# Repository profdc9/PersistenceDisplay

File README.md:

Persistence Display.  More details to come soon.

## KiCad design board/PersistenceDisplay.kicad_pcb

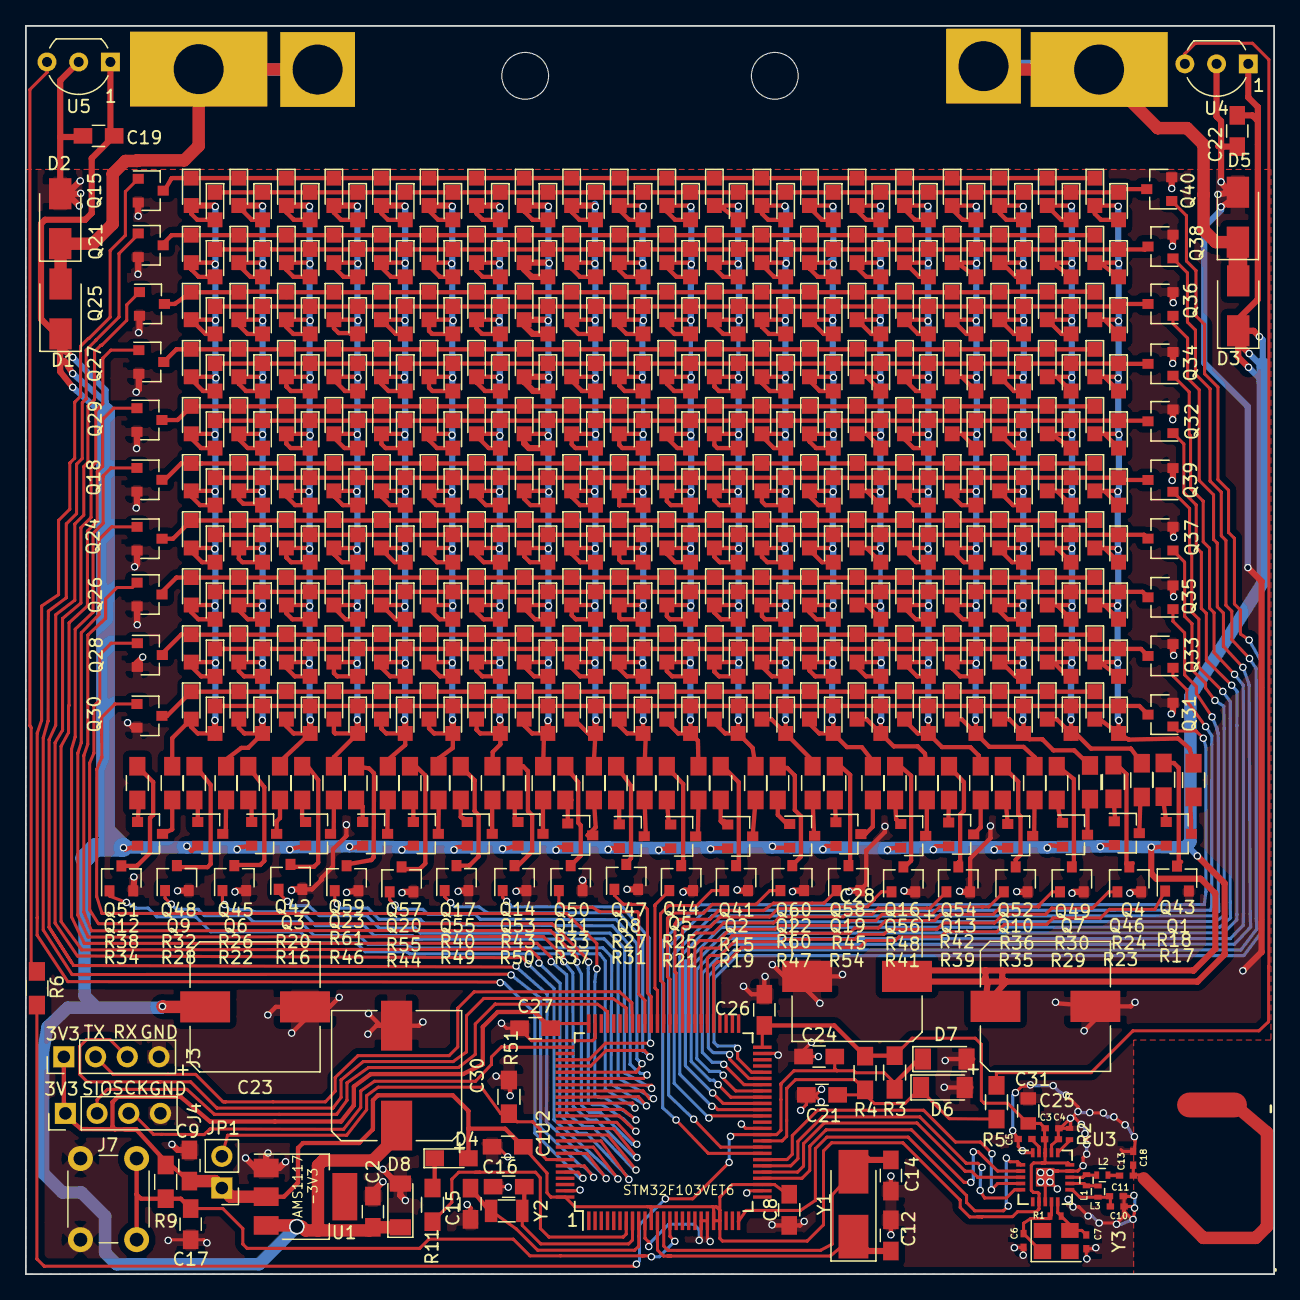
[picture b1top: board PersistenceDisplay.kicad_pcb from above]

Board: 2 copper layers, 100.0 x 100.0 mm, 567 parts (0 on the bottom side), 175 nets.

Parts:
C1, C2: 1 uF; C_0805_HandSoldering
C3: 10 nF; C_0402_NoSilk
C4: 1 nF; C_0402_NoSilk
C5: 33 nF; C_0402_NoSilk
C6, C7: 22 pF; C_0402_NoSilk
C8, C9, C19, C22, C26, C27: 0.1 uF; C_0805_HandSoldering
C10: 2.2 nF; C_0402_NoSilk
C11: 4.7 pF; C_0402_NoSilk
C12, C14, C15, C16: 20 pF; C_0805_HandSoldering
C13: 1.5 pF; C_0402_NoSilk
C17: 10 nF; C_0805_HandSoldering
C18: 1 pF; C_0402_NoSilk
C21, C24: 22 pF; C_0805_HandSoldering
C23, C25, C28, C30: 1000 uF; CP_Elec_10x10.5
C31: 4.7 uF; C_0805
D1, D2, D3, D5: SS34; D_SMA
D4: LED; LED_0805_HandSoldering
D6, D7: 3.3V; D_MiniMELF
D8: 5.6V; D_MiniMELF
D9, D10, D11, D12, D13, D14, D15, D16, D17, D18, D19, D20, D21, D22, D23, D24, D25, D26, D27, D28, D29, D30, D31, D32, D33, D34, D35, D36, D37, D38, D39, D40, D41, D42, D43, D44, D45, D46, D47, D48, D49, D50, D51, D52, D53, D54, D55, D56, D57, D58, D59, D60, D61, D62, D63, D64, D65, D66, D67, D68, D69, D70, D71, D72, D73, D74, D75, D76, D77, D78, D79, D80, D81, D82, D83, D84, D85, D86, D87, D88, D89, D90, D91, D92, D93, D94, D95, D96, D97, D98, D99, D100, D101, D102, D103, D104, D105, D106, D107, D108, D109, D110, D111, D112, D113, D114, D115, D116, D117, D118, D119, D120, D121, D122, D123, D124, D125, D126, D127, D128, D129, D130, D131, D132, D133, D134, D135, D136, D137, D138, D139, D140, D141, D142, D143, D144, D145, D146, D147, D148, D149, D150, D151, D152, D153, D154, D155, D156, D157, D158, D159, D160, D161, D162, D163, D164, D165, D166, D167, D168, D169, D170, D171, D172, D173, D174, D175, D176, D177, D178, D179, D180, D181, D182, D183, D184, D185, D186, D187, D188, D189, D190, D191, D192, D193, D194, D195, D196, D197, D198, D199, D200, D201, D202, D203, D204, D205, D206, D207, D208, D209, D210, D211, D212, D213, D214, D215, D216, D217, D218, D219, D220, D221, D222, D223, D224, D225, D226, D227, D228, D229, D230, D231, D232, D233, D234, D235, D236, D237, D238, D239, D240, D241, D242, D243, D244, D245, D246, D247, D248, D249, D250, D251, D252, D253, D254, D255, D256, D257, D258, D259, D260, D261, D262, D263, D264, D265, D266, D267, D268, D269, D270, D271, D272, D273, D274, D275, D276, D277, D278, D279, D280, D281, D282, D283, D284, D285, D286, D287, D288, D289, D290, D291, D292, D293, D294, D295, D296, D297, D298, D299, D300, D301, D302, D303, D304, D305, D306, D307, D308, D309, D310, D311, D312, D313, D314, D315, D316, D317, D318, D319, D320, D321, D322, D323, D324, D325, D326, D327, D328, D329, D330, D331, D332, D333, D334, D335, D336, D337, D338, D339, D340, D341, D342, D343, D344, D345, D346, D347, D348, D349, D350, D351, D352, D353, D354, D355, D356, D357, D358, D359, D360, D361, D362, D363, D364, D365, D366, D367, D368, D369, D370, D371, D372, D373, D374, D375, D376, D377, D378, D379, D380, D381, D382, D383, D384, D385, D386, D387, D388, D389, D390, D391, D392, D393, D394, D395, D396, D397, D398, D399, D400, D401, D402, D403, D404, D405, D406, D407, D408: LED; LED_0805NoLabel
J3, J4: Conn_01x04; Pin_Header_Straight_1x04_Pitch2.54mm
J5, J6, J11, J12: Conn_01x01; ContactPad
J7: Conn_01x02; SW_PUSH_6mm
J8, J9: Conn_01x01; BigSlot
JP1: Jumper; Pin_Header_Straight_1x02_Pitch2.54mm
L1: 8.2 nH; L_0402
L2: 3.9 nH; L_0402
L3: 2.7 nH; L_0402
Q1, Q2, Q3, Q4, Q5, Q6, Q7, Q8, Q9, Q10, Q11, Q12, Q13, Q14, Q15, Q16, Q17, Q18, Q19, Q20, Q21, Q22, Q23, Q24, Q25, Q26, Q27, Q28, Q29, Q30, Q31, Q32, Q33, Q34, Q35, Q36, Q37, Q38, Q39, Q40: 2N7002; SOT-23
Q41, Q42, Q43, Q44, Q45, Q46, Q47, Q48, Q49, Q50, Q51, Q52, Q53, Q54, Q55, Q56, Q57, Q58, Q59, Q60: SS8550; SOT-23
R1: 1M; R_0402_NoSilk
R2: 22k; R_0402_NoSilk
R3, R4: 1k; R_0805_HandSoldering
R5, R6: 150R; R_0805_HandSoldering
R9: 1.5k; R_0805_HandSoldering
R11: 470R; R_0805_HandSoldering
R15, R16, R17, R21, R22, R23, R27, R28, R29, R33, R34, R35, R39, R40, R41, R44, R45, R46, R47, R50: 220R; R_0805_HandSoldering
R18, R19, R20, R24, R25, R26, R30, R31, R32, R36, R37, R38, R42, R43, R48, R49, R51, R54, R55, R60, R61: 10k; R_0805_HandSoldering
U1: AMS1117-3V3; SOT-223
U2: STM32F103VETx; LQFP-100_14x14mm_Pitch0.5mm
U3: nrf24l01; QFN-20-1EP_4x4mm_Pitch0.5mm_smaller_internal_pad
U4, U5: OH137; TO-92_Inline_Wide
Y1: 8 MHz; Crystal_SMD_5032-2pin_5.0x3.2mm_HandSoldering
Y2: 32.768 kHz; Crystal_SMD_3215-2pin_3.2x1.5mm
Y3: 16 MHz; Crystal_SMD_3225-4pin_3.2x2.5mm

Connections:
+3V3: C1.2, C3.2, C4.2, C8.2, C9.2, C26.2, C27.2, C31.2, D4.2, J3.1, J4.1, JP1.1, R3.2, R4.2, R9.1, U1.2, U2.11, U2.21, U2.22, U2.28, U2.50, U2.75, U2.100, U3.7, U3.15, U3.18
+5V: C2.2, C19.2, C22.2, C23.1, C25.1, C28.1, C30.1, D1.1, D3.1, D8.1, Q41.2, Q42.2, Q43.2, Q44.2, Q45.2, Q46.2, Q47.2, Q48.2, Q49.2, Q50.2, Q51.2, Q52.2, Q53.2, Q54.2, Q55.2, Q56.2, Q57.2, Q58.2, Q59.2, Q60.2, U1.3, U4.1, U5.1
COL1: D9.2, D29.2, D49.2, D69.2, D89.2, D109.2, D129.2, D149.2, D169.2, D189.2, D209.2, D229.2, D249.2, D269.2, D289.2, D309.2, D329.2, D349.2, D369.2, D389.2, R17.2
COL2: D10.2, D30.2, D50.2, D70.2, D90.2, D110.2, D130.2, D150.2, D170.2, D190.2, D210.2, D230.2, D250.2, D270.2, D290.2, D310.2, D330.2, D350.2, D370.2, D390.2, R23.2
COL3: D11.2, D31.2, D51.2, D71.2, D91.2, D111.2, D131.2, D151.2, D171.2, D191.2, D211.2, D231.2, D251.2, D271.2, D291.2, D311.2, D331.2, D351.2, D371.2, D391.2, R29.2
COL4: D12.2, D32.2, D52.2, D72.2, D92.2, D112.2, D132.2, D152.2, D172.2, D192.2, D212.2, D232.2, D252.2, D272.2, D292.2, D312.2, D332.2, D352.2, D372.2, D392.2, R35.2
COL5: D13.2, D33.2, D53.2, D73.2, D93.2, D113.2, D133.2, D153.2, D173.2, D193.2, D213.2, D233.2, D253.2, D273.2, D293.2, D313.2, D333.2, D353.2, D373.2, D393.2, R39.2
COL6: D14.2, D34.2, D54.2, D74.2, D94.2, D114.2, D134.2, D154.2, D174.2, D194.2, D214.2, D234.2, D254.2, D274.2, D294.2, D314.2, D334.2, D354.2, D374.2, D394.2, R41.2
COL7: D15.2, D35.2, D55.2, D75.2, D95.2, D115.2, D135.2, D155.2, D175.2, D195.2, D215.2, D235.2, D255.2, D275.2, D295.2, D315.2, D335.2, D355.2, D375.2, D395.2, R45.2
COL8: D16.2, D36.2, D56.2, D76.2, D96.2, D116.2, D136.2, D156.2, D176.2, D196.2, D216.2, D236.2, D256.2, D276.2, D296.2, D316.2, D336.2, D356.2, D376.2, D396.2, R47.2
COL9: D17.2, D37.2, D57.2, D77.2, D97.2, D117.2, D137.2, D157.2, D177.2, D197.2, D217.2, D237.2, D257.2, D277.2, D297.2, D317.2, D337.2, D357.2, D377.2, D397.2, R15.2
COL10: D18.2, D38.2, D58.2, D78.2, D98.2, D118.2, D138.2, D158.2, D178.2, D198.2, D218.2, D238.2, D258.2, D278.2, D298.2, D318.2, D338.2, D358.2, D378.2, D398.2, R21.2
COL11: D19.2, D39.2, D59.2, D79.2, D99.2, D119.2, D139.2, D159.2, D179.2, D199.2, D219.2, D239.2, D259.2, D279.2, D299.2, D319.2, D339.2, D359.2, D379.2, D399.2, R27.2
COL12: D20.2, D40.2, D60.2, D80.2, D100.2, D120.2, D140.2, D160.2, D180.2, D200.2, D220.2, D240.2, D260.2, D280.2, D300.2, D320.2, D340.2, D360.2, D380.2, D400.2, R33.2
COL13: D21.2, D41.2, D61.2, D81.2, D101.2, D121.2, D141.2, D161.2, D181.2, D201.2, D221.2, D241.2, D261.2, D281.2, D301.2, D321.2, D341.2, D361.2, D381.2, D401.2, R50.2
COL14: D22.2, D42.2, D62.2, D82.2, D102.2, D122.2, D142.2, D162.2, D182.2, D202.2, D222.2, D242.2, D262.2, D282.2, D302.2, D322.2, D342.2, D362.2, D382.2, D402.2, R40.2
COL15: D23.2, D43.2, D63.2, D83.2, D103.2, D123.2, D143.2, D163.2, D183.2, D203.2, D223.2, D243.2, D263.2, D283.2, D303.2, D323.2, D343.2, D363.2, D383.2, D403.2, R44.2
COL16: D24.2, D44.2, D64.2, D84.2, D104.2, D124.2, D144.2, D164.2, D184.2, D204.2, D224.2, D244.2, D264.2, D284.2, D304.2, D324.2, D344.2, D364.2, D384.2, D404.2, R46.2
COL17: D25.2, D45.2, D65.2, D85.2, D105.2, D125.2, D145.2, D165.2, D185.2, D205.2, D225.2, D245.2, D265.2, D285.2, D305.2, D325.2, D345.2, D365.2, D385.2, D405.2, R16.2
COL18: D26.2, D46.2, D66.2, D86.2, D106.2, D126.2, D146.2, D166.2, D186.2, D206.2, D226.2, D246.2, D266.2, D286.2, D306.2, D326.2, D346.2, D366.2, D386.2, D406.2, R22.2
COL19: D27.2, D47.2, D67.2, D87.2, D107.2, D127.2, D147.2, D167.2, D187.2, D207.2, D227.2, D247.2, D267.2, D287.2, D307.2, D327.2, D347.2, D367.2, D387.2, D407.2, R28.2
COL20: D28.2, D48.2, D68.2, D88.2, D108.2, D128.2, D148.2, D168.2, D188.2, D208.2, D228.2, D248.2, D268.2, D288.2, D308.2, D328.2, D348.2, D368.2, D388.2, D408.2, R34.2
GND: C1.1, C2.1, C3.1, C4.1, C5.1, C6.1, C7.1, C8.1, C9.1, C10.1, C11.1, C12.2, C14.2, C15.2, C16.2, C17.2, C18.1, C19.1, C21.1, C22.1, C23.2, C24.1, C25.2, C26.1, C27.1, C28.2, C30.2, C31.1, D2.2, D5.2, D6.2, D7.2, D8.2, J3.4, J4.4, J7.2, Q1.2, Q2.2, Q3.2, Q4.2, Q5.2, Q6.2, Q7.2, Q8.2, Q9.2, Q10.2, Q11.2, Q12.2, Q13.2, Q14.2, Q15.2, Q16.2, Q17.2, Q18.2, Q19.2, Q20.2, Q21.2, Q22.2, Q23.2, Q24.2, Q25.2, Q26.2, Q27.2, Q28.2, Q29.2, Q30.2, Q31.2, Q32.2, Q33.2, Q34.2, Q35.2, Q36.2, Q37.2, Q38.2, Q39.2, Q40.2, R2.1, R51.1, U1.1, U2.10, U2.19, U2.20, U2.27, U2.37, U2.49, U2.74, U2.99, U3.8, U3.14, U3.17, U3.20, U3.21, U4.2, U5.2
NRST: C17.1, J7.1, R9.2, U2.14
unnamed: C5.2, U3.19
unnamed: C6.2, R1.2, U3.9, Y3.1
unnamed: C7.2, R1.1, U3.10, Y3.3
unnamed: C10.2, C11.2, L3.1, U3.11
unnamed: C13.1, L2.1
unnamed: C13.2, C18.2
unnamed: D1.2, D2.1, J5.1, J11.1
unnamed: D3.2, D5.1, J6.1, J12.1
unnamed: D4.1, R11.2
unnamed: JP1.2, R51.2, U2.94
unnamed: L1.1, L3.2, U3.12
unnamed: L1.2, L2.2, U3.13
unnamed: Q1.3, R18.1
unnamed: Q2.3, R19.1
unnamed: Q3.3, R20.1
unnamed: Q4.3, R24.1
unnamed: Q5.3, R25.1
unnamed: Q6.3, R26.1
unnamed: Q7.3, R30.1
unnamed: Q8.3, R31.1
unnamed: Q9.3, R32.1
unnamed: Q10.3, R36.1
unnamed: Q11.3, R37.1
unnamed: Q12.3, R38.1
unnamed: Q13.3, R42.1
unnamed: Q14.3, R43.1
unnamed: Q16.3, R48.1
unnamed: Q17.3, R49.1
unnamed: Q19.3, R54.1
unnamed: Q20.3, R55.1
unnamed: Q22.3, R60.1
unnamed: Q23.3, R61.1
unnamed: Q41.1, R19.2
unnamed: Q41.3, R15.1
unnamed: Q42.1, R20.2
unnamed: Q42.3, R16.1
unnamed: Q43.1, R18.2
unnamed: Q43.3, R17.1
unnamed: Q44.1, R25.2
unnamed: Q44.3, R21.1
unnamed: Q45.1, R26.2
unnamed: Q45.3, R22.1
unnamed: Q46.1, R24.2
unnamed: Q46.3, R23.1
unnamed: Q47.1, R31.2
unnamed: Q47.3, R27.1
unnamed: Q48.1, R32.2
unnamed: Q48.3, R28.1
unnamed: Q49.1, R30.2
unnamed: Q49.3, R29.1
unnamed: Q50.1, R37.2
unnamed: Q50.3, R33.1
unnamed: Q51.1, R38.2
unnamed: Q51.3, R34.1
unnamed: Q52.1, R36.2
unnamed: Q52.3, R35.1
unnamed: Q53.1, R43.2
unnamed: Q53.3, R50.1
unnamed: Q54.1, R42.2
unnamed: Q54.3, R39.1
unnamed: Q55.1, R49.2
unnamed: Q55.3, R40.1
unnamed: Q56.1, R48.2
unnamed: Q56.3, R41.1
unnamed: Q57.1, R55.2
unnamed: Q57.3, R44.1
unnamed: Q58.1, R54.2
unnamed: Q58.3, R45.1
unnamed: Q59.1, R61.2
unnamed: Q59.3, R46.1
unnamed: Q60.1, R60.2
unnamed: Q60.3, R47.1
unnamed: R2.2, U3.16
unnamed: R5.1, U4.3
unnamed: R6.1, U5.3
OSC32IN: C15.1, U2.9, Y2.2
OSC32OUT: C16.1, U2.8, Y2.1
OSCIN: C12.1, U2.12, Y1.1
OSCOUT: C14.1, U2.13, Y1.2
PA2: U2.25, U3.1
PA4: U2.29, U3.2
PA5: U2.30, U3.3
PA6: U2.31, U3.5
PA7: U2.32, U3.4
PA9: J3.2, U2.68
PA10: J3.3, U2.69
PA13: J4.2, U2.72
PA14: J4.3, U2.76
PB0: C21.2, D6.1, R4.1, R5.2, U2.35
PB1: C24.2, D7.1, R3.1, R6.2, U2.36
PB3: Q24.1, U2.89
PB4: Q18.1, U2.90
PB5: Q29.1, U2.91
PB6: Q27.1, U2.92
PB7: Q25.1, U2.93
PB8: Q21.1, U2.95
PB9: Q15.1, U2.96
PC4: Q31.1, U2.33
PC5: Q33.1, U2.34
PC6: Q2.1, U2.63
PC7: Q5.1, U2.64
PC8: Q8.1, U2.65
PC9: Q11.1, U2.66
PC10: Q14.1, U2.78
PC11: Q17.1, U2.79
PC12: Q20.1, U2.80
PC13: R11.1, U2.7
PD0: Q23.1, U2.81
PD1: Q3.1, U2.82
PD2: Q6.1, U2.83
PD3: Q9.1, U2.84
PD4: Q12.1, U2.85
PD5: Q30.1, U2.86
PD6: Q28.1, U2.87
PD7: Q26.1, U2.88
PD8: Q1.1, U2.55
PD9: Q4.1, U2.56
PD10: Q7.1, U2.57
PD11: Q10.1, U2.58
PD12: Q13.1, U2.59
PD13: Q16.1, U2.60
PD14: Q19.1, U2.61
PD15: Q22.1, U2.62
PE8: Q35.1, U2.39
PE9: Q37.1, U2.40
PE10: Q39.1, U2.41
PE11: Q32.1, U2.42
PE12: Q34.1, U2.43
PE13: Q36.1, U2.44
PE14: Q38.1, U2.45
PE15: Q40.1, U2.46
ROW1: D9.1, D10.1, D11.1, D12.1, D13.1, D14.1, D15.1, D16.1, D17.1, D18.1, D19.1, D20.1, D21.1, D22.1, D23.1, D24.1, D25.1, D26.1, D27.1, D28.1, Q15.3
ROW2: D49.1, D50.1, D51.1, D52.1, D53.1, D54.1, D55.1, D56.1, D57.1, D58.1, D59.1, D60.1, D61.1, D62.1, D63.1, D64.1, D65.1, D66.1, D67.1, D68.1, Q21.3
ROW3: D89.1, D90.1, D91.1, D92.1, D93.1, D94.1, D95.1, D96.1, D97.1, D98.1, D99.1, D100.1, D101.1, D102.1, D103.1, D104.1, D105.1, D106.1, D107.1, D108.1, Q25.3
ROW4: D129.1, D130.1, D131.1, D132.1, D133.1, D134.1, D135.1, D136.1, D137.1, D138.1, D139.1, D140.1, D141.1, D142.1, D143.1, D144.1, D145.1, D146.1, D147.1, D148.1, Q27.3
ROW5: D169.1, D170.1, D171.1, D172.1, D173.1, D174.1, D175.1, D176.1, D177.1, D178.1, D179.1, D180.1, D181.1, D182.1, D183.1, D184.1, D185.1, D186.1, D187.1, D188.1, Q29.3
ROW6: D209.1, D210.1, D211.1, D212.1, D213.1, D214.1, D215.1, D216.1, D217.1, D218.1, D219.1, D220.1, D221.1, D222.1, D223.1, D224.1, D225.1, D226.1, D227.1, D228.1, Q18.3
ROW7: D249.1, D250.1, D251.1, D252.1, D253.1, D254.1, D255.1, D256.1, D257.1, D258.1, D259.1, D260.1, D261.1, D262.1, D263.1, D264.1, D265.1, D266.1, D267.1, D268.1, Q24.3
ROW8: D289.1, D290.1, D291.1, D292.1, D293.1, D294.1, D295.1, D296.1, D297.1, D298.1, D299.1, D300.1, D301.1, D302.1, D303.1, D304.1, D305.1, D306.1, D307.1, D308.1, Q26.3
ROW9: D329.1, D330.1, D331.1, D332.1, D333.1, D334.1, D335.1, D336.1, D337.1, D338.1, D339.1, D340.1, D341.1, D342.1, D343.1, D344.1, D345.1, D346.1, D347.1, D348.1, Q28.3
ROW10: D369.1, D370.1, D371.1, D372.1, D373.1, D374.1, D375.1, D376.1, D377.1, D378.1, D379.1, D380.1, D381.1, D382.1, D383.1, D384.1, D385.1, D386.1, D387.1, D388.1, Q30.3
ROW11: D389.1, D390.1, D391.1, D392.1, D393.1, D394.1, D395.1, D396.1, D397.1, D398.1, D399.1, D400.1, D401.1, D402.1, D403.1, D404.1, D405.1, D406.1, D407.1, D408.1, Q31.3
ROW12: D349.1, D350.1, D351.1, D352.1, D353.1, D354.1, D355.1, D356.1, D357.1, D358.1, D359.1, D360.1, D361.1, D362.1, D363.1, D364.1, D365.1, D366.1, D367.1, D368.1, Q33.3
ROW13: D309.1, D310.1, D311.1, D312.1, D313.1, D314.1, D315.1, D316.1, D317.1, D318.1, D319.1, D320.1, D321.1, D322.1, D323.1, D324.1, D325.1, D326.1, D327.1, D328.1, Q35.3
ROW14: D269.1, D270.1, D271.1, D272.1, D273.1, D274.1, D275.1, D276.1, D277.1, D278.1, D279.1, D280.1, D281.1, D282.1, D283.1, D284.1, D285.1, D286.1, D287.1, D288.1, Q37.3
ROW15: D229.1, D230.1, D231.1, D232.1, D233.1, D234.1, D235.1, D236.1, D237.1, D238.1, D239.1, D240.1, D241.1, D242.1, D243.1, D244.1, D245.1, D246.1, D247.1, D248.1, Q39.3
ROW16: D189.1, D190.1, D191.1, D192.1, D193.1, D194.1, D195.1, D196.1, D197.1, D198.1, D199.1, D200.1, D201.1, D202.1, D203.1, D204.1, D205.1, D206.1, D207.1, D208.1, Q32.3
ROW17: D149.1, D150.1, D151.1, D152.1, D153.1, D154.1, D155.1, D156.1, D157.1, D158.1, D159.1, D160.1, D161.1, D162.1, D163.1, D164.1, D165.1, D166.1, D167.1, D168.1, Q34.3
ROW18: D109.1, D110.1, D111.1, D112.1, D113.1, D114.1, D115.1, D116.1, D117.1, D118.1, D119.1, D120.1, D121.1, D122.1, D123.1, D124.1, D125.1, D126.1, D127.1, D128.1, Q36.3
ROW19: D69.1, D70.1, D71.1, D72.1, D73.1, D74.1, D75.1, D76.1, D77.1, D78.1, D79.1, D80.1, D81.1, D82.1, D83.1, D84.1, D85.1, D86.1, D87.1, D88.1, Q38.3
ROW20: D29.1, D30.1, D31.1, D32.1, D33.1, D34.1, D35.1, D36.1, D37.1, D38.1, D39.1, D40.1, D41.1, D42.1, D43.1, D44.1, D45.1, D46.1, D47.1, D48.1, Q40.3

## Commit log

2020-05-18 Moved around components and added cutouts
2020-05-18 Changed PCB picture
2020-05-19 Correct schematic
2020-05-20 Moved the brushes to the other side of the board
2020-05-20 JLCPCB order 2020-05-20
2020-07-09 Added board holder FreeCAD file
2020-07-09 Changed to using hall effect sensors

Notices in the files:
board/PersistenceDisplay.kicad_pcb:
CC-BY-SA 4.0
